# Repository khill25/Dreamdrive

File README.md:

# Dreamdrive
Retro gaming accessories produced by Dreamcraft Industries. Dreamdrive is coming to disc based systems called Dreamdisc! Dreamcast is the first console to get this treatment. Work is in progress to finalize the hardware and software for a first producion run. Stay tuned!

## [Discord](https://discord.gg/sHbhx2qJuK)
Join the discussion and get the latest on Dreamdrive status. Chat with other hackers. Have ideas on a new Dreamdrive product? Come and let me know. 

# Dreamdumper64
New Dreamdumper64 hardware files have been checked in! Navigate to `N64/hw/cart_tester/pc64` for the latest kicad project files.

# Projects
Current project status

| Project | Platform | Purpose  | Status | Notes |
| ------------- | ------------- | ------------- | ------------- | ------------- |
| Dreamdumper64 | N64 | Backup your cartridges | Finished | Completed units are available [here](https://dreamcraftindustries.com/products/dreamdumper64-assembled)!|
| Dreamdisc | Dreamcast | Dreamdive ODE For Dreamcast | Prototype/v3 | Repo files wont boot yet but the design has been verified and will be available soon |
| Dreamdrive Advance | GBA | Developer rom cart | Prototype/v2 | Waiting for new board designs with support for faster psram. Current PSRAM on the qspi bus isn't fast enough to service the cart |
| Super Dreamdrive | SNES | Developer rom cart | Prototype/v1 | Drafted prototype hardware and software. No idea if this is working |

### License
This project is licensed under the [Dreamdrive Open Hardware License v1.0](./LICENSE).  
You are free to learn from, modify, and remix this design for non-commercial purposes with attribution.  
Commercial use requires permission — reach out to kaili [at] dreamcraftindustries [dot] com.

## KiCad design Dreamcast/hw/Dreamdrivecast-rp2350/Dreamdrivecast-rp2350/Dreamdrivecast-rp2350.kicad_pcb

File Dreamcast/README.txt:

Dreamcast GD-ROM replacement. WIP! Untested and not in production state!!!

Will use RP2040s and SD Card to emulate the gdrom drive.

LICENSE: BSD-2-Clause
Copyright (c) 2023 Kaili Hill

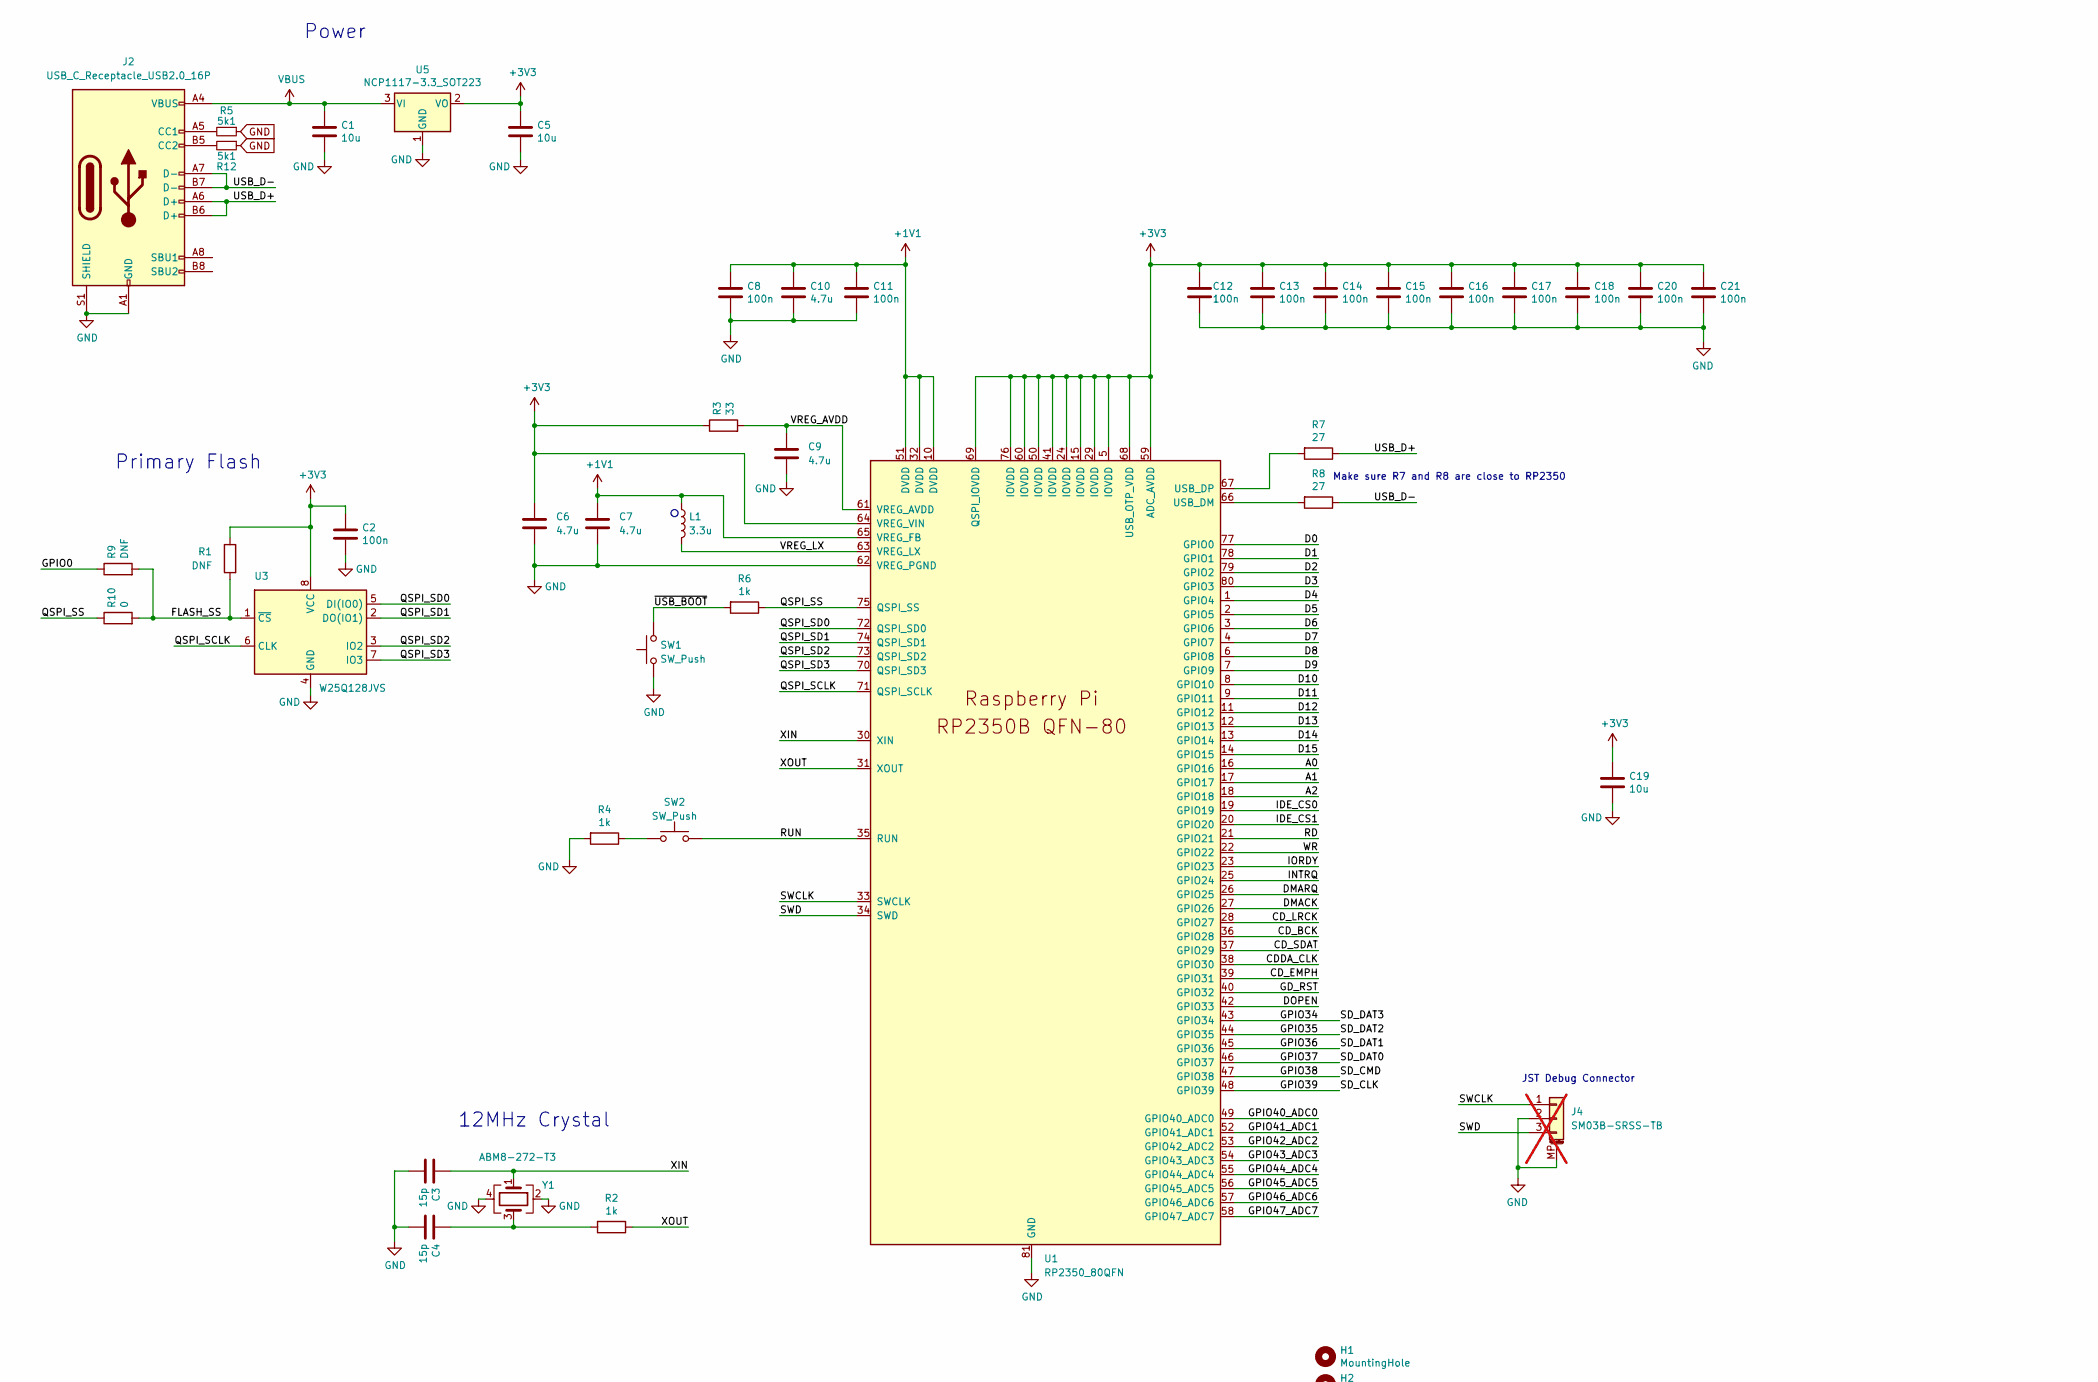
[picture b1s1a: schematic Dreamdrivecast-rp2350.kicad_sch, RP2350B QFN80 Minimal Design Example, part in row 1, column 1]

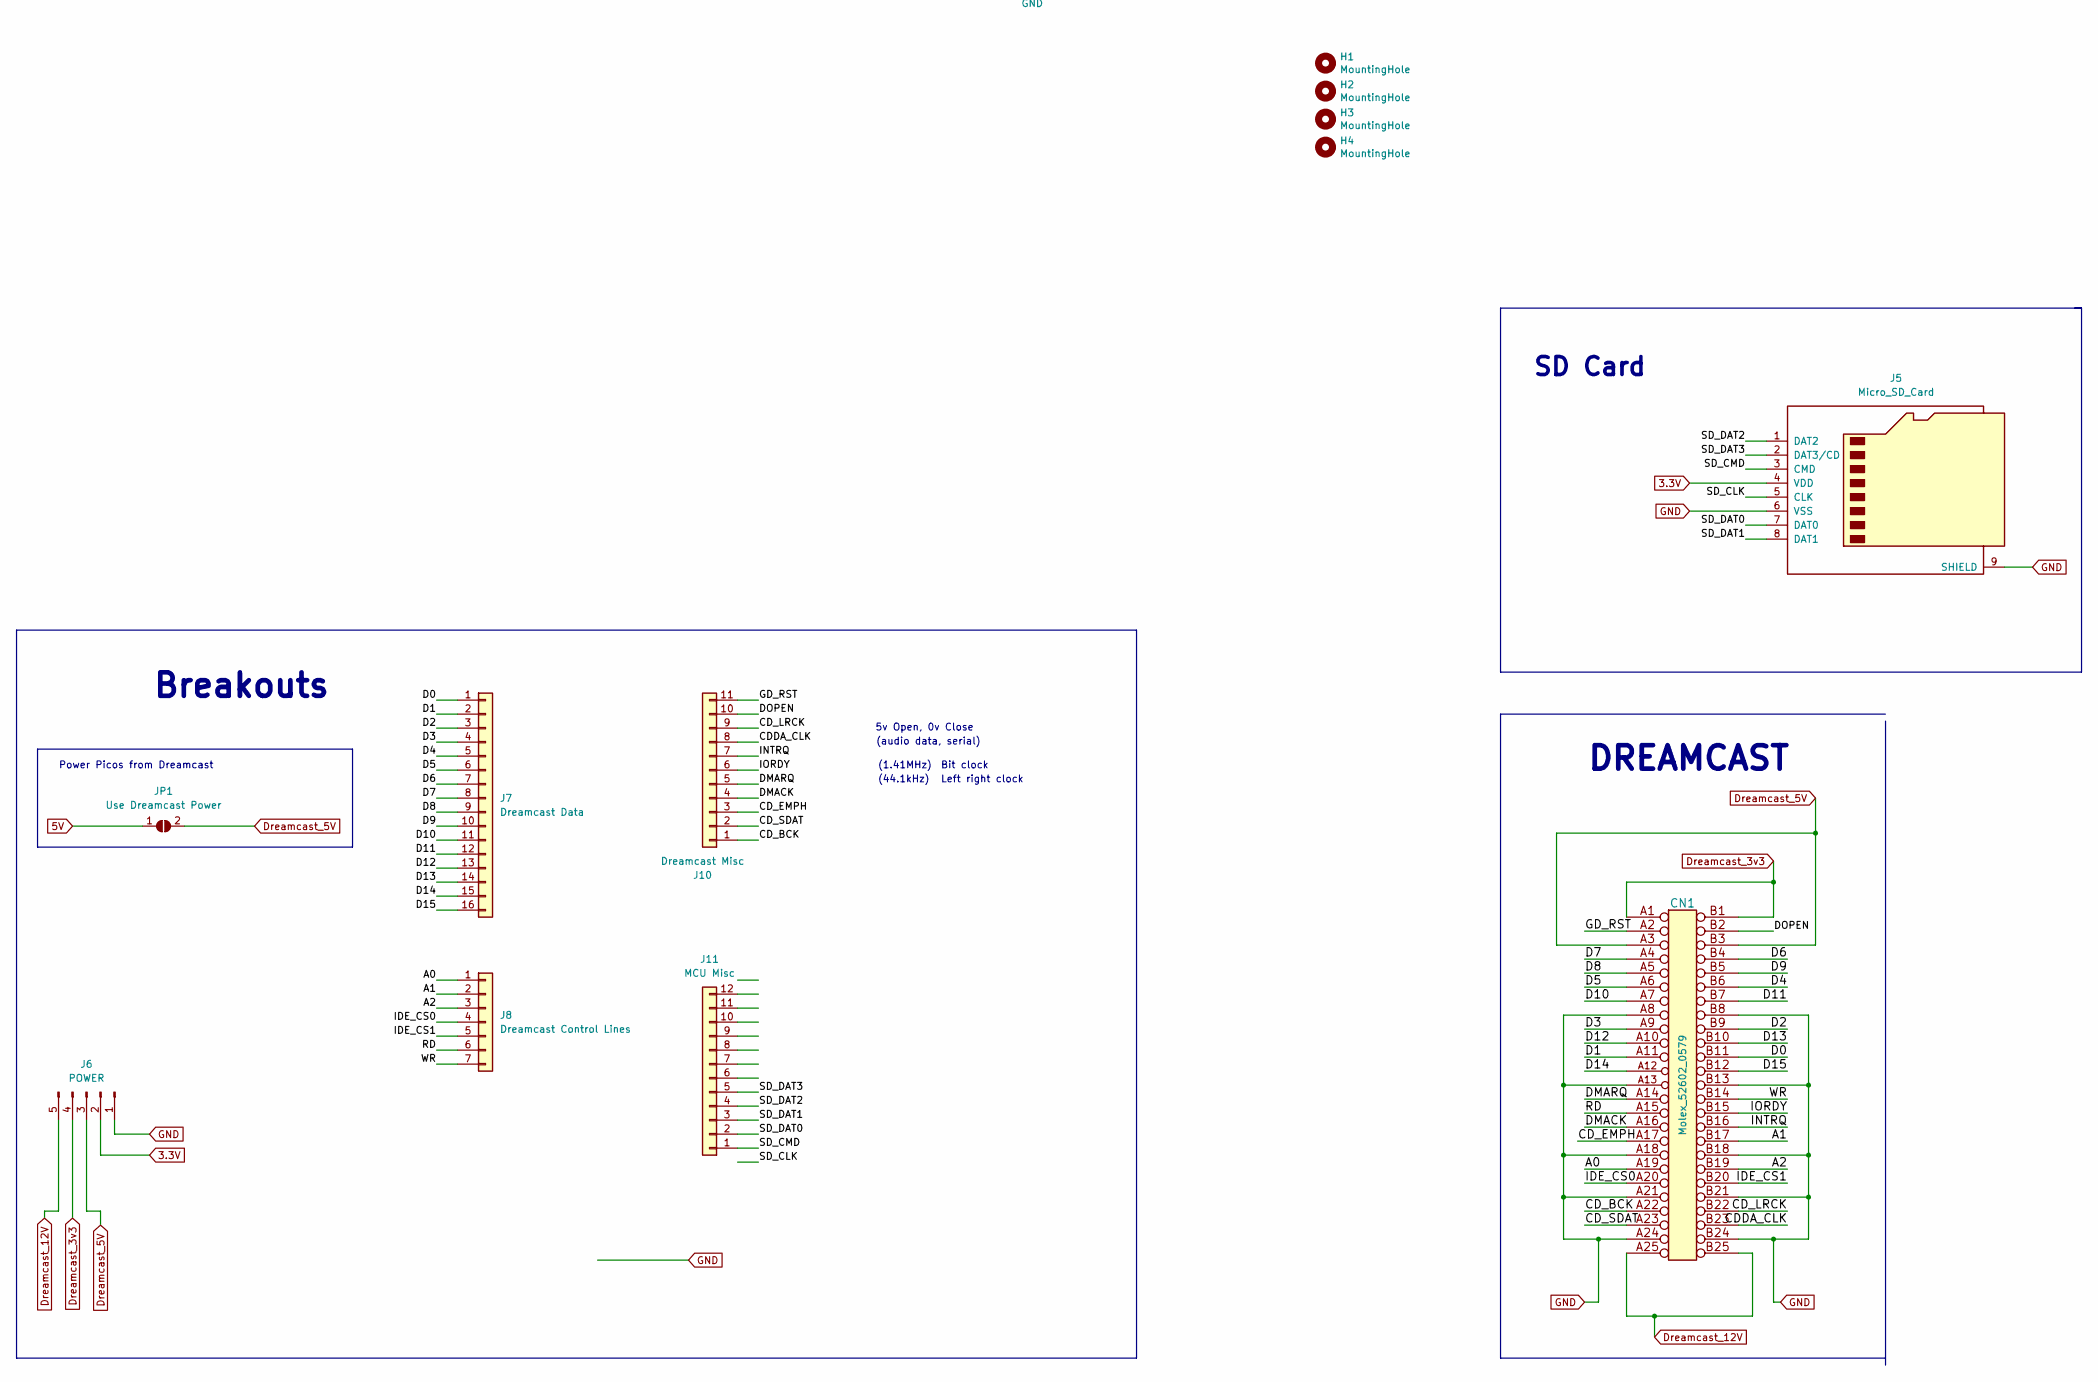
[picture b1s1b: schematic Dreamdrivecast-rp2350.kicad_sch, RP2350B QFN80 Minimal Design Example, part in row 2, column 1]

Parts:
C1, C5, C19: 10u; C_0805_2012Metric
C2, C8, C11, C12, C13, C14, C15, C16, C17, C18, C20, C21: 100n; C_0402_1005Metric
C3, C4: 15p; C_0402_1005Metric
C6, C7: 4.7u; C_0402_1005Metric_small_pads
C9, C10: 4.7u; C_0402_1005Metric
CN1: Molex_52602_0579; LCSC C588209
H1, H2, H3, H4: MountingHole; MountingHole_2.7mm_M2.5
J2: USB_C_Receptacle_USB2.0_16P; USB_C_Receptacle_HRO_TYPE-C-31-M-12
J4: SM03B-SRSS-TB; JST_SH_SM03B-SRSS-TB_1x03-1MP_P1.00mm_Horizontal; not fitted
J5: Micro_SD_Card; microSD_HC_Molex_104031-0811; MPN 1040310811; LCSC C585350
J6: POWER; PinHeader_1x05_P2.54mm_Vertical
J7: Dreamcast Data; PinHeader_1x16_P2.54mm_Vertical
J8: Dreamcast Control Lines; PinHeader_2x07_P2.54mm_Vertical_SMD
J10: Dreamcast Misc; PinHeader_1x11_P2.54mm_Vertical
J11: MCU Misc; PinHeader_1x12_P2.54mm_Vertical
JP1: Use Dreamcast Power; SolderJumper-2_P1.3mm_Open_RoundedPad1.0x1.5mm
L1: 3.3u; L_pol_2016
R1, R9: DNF; R_0402_1005Metric
R2, R4, R6: 1k; R_0402_1005Metric
R3: 33; R_0402_1005Metric
R5, R12: 5k1; R_0402_1005Metric; LCSC C25905
R7, R8: 27; R_0402_1005Metric
R10: 0; R_0402_1005Metric
SW1, SW2: SW_Push; SW_Push_1P1T_NO_Vertical_Wuerth_434133025816
U1: RP2350_80QFN; RP2350-QFN-80-1EP_10x10_P0.4mm_EP3.4x3.4mm_ThermalVias
U3: W25Q128JVS; SOIC-8_5.23x5.23mm_P1.27mm
U5: NCP1117-3.3_SOT223; SOT-223-3_TabPin2
Y1: ABM8-272-T3; Crystal_SMD_3225-4Pin_3.2x2.5mm

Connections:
3.3V: J5.4 (VDD), J6.2
5V: JP1.1 (A)
+1V1: C7.1, C8.1, C10.1, C11.1, L1.1, U1.10 (DVDD), U1.32 (DVDD), U1.51 (DVDD), U1.65 (VREG_FB)
+3V3: C2.1, C5.1, C6.1, C12.1, C13.1, C14.1, C15.1, C16.1, C17.1, C18.1, C19.1, C20.1, C21.1, R1.1, R3.1, U1.5 (IOVDD), U1.15 (IOVDD), U1.24 (IOVDD), U1.29 (IOVDD), U1.41 (IOVDD), U1.50 (IOVDD), U1.59 (ADC_AVDD), U1.60 (IOVDD), U1.64 (VREG_VIN), U1.68 (USB_OTP_VDD), U1.69 (QSPI_IOVDD), U1.76 (IOVDD), U3.8 (VCC), U5.2 (VO)
/A0: CN1.A19, J8.1, U1.16 (GPIO16)
/A1: CN1.B17, J8.2, U1.17 (GPIO17)
/A2: CN1.B19, J8.3, U1.18 (GPIO18)
/CDDA_CLK: CN1.B23, J10.8, U1.38 (GPIO30)
/CD_BCK: CN1.A22, J10.1, U1.36 (GPIO28)
/CD_EMPH: CN1.A17, J10.3, U1.39 (GPIO31)
/CD_LRCK: CN1.B22, J10.9, U1.28 (GPIO27)
/CD_SDAT: CN1.A23, J10.2, U1.37 (GPIO29)
/D0: CN1.B11, J7.1, U1.77 (GPIO0)
/D1: CN1.A11, J7.2, U1.78 (GPIO1)
/D2: CN1.B9, J7.3, U1.79 (GPIO2)
/D3: CN1.A9, J7.4, U1.80 (GPIO3)
/D4: CN1.B6, J7.5, U1.1 (GPIO4)
/D5: CN1.A6, J7.6, U1.2 (GPIO5)
/D6: CN1.B4, J7.7, U1.3 (GPIO6)
/D7: CN1.A4, J7.8, U1.4 (GPIO7)
/D8: CN1.A5, J7.9, U1.6 (GPIO8)
/D9: CN1.B5, J7.10, U1.7 (GPIO9)
/D10: CN1.A7, J7.11, U1.8 (GPIO10)
/D11: CN1.B7, J7.12, U1.9 (GPIO11)
/D12: CN1.A10, J7.13, U1.11 (GPIO12)
/D13: CN1.B10, J7.14, U1.12 (GPIO13)
/D14: CN1.A12, J7.15, U1.13 (GPIO14)
/D15: CN1.B12, J7.16, U1.14 (GPIO15)
/DMACK: CN1.A16, J10.4, U1.27 (GPIO26)
/DMARQ: CN1.A14, J10.5, U1.26 (GPIO25)
/DOPEN: CN1.B2, J10.10, U1.42 (GPIO33)
/FLASH_SS: R1.2, R9.2, R10.2, U3.1 (~CS)
/GD_RST: CN1.A2, J10.11, U1.40 (GPIO32)
/GPIO0: R9.1
/GPIO34: J5.2 (DAT3/CD), J11.5, U1.43 (GPIO34)
/GPIO35: J5.1 (DAT2), J11.4, U1.44 (GPIO35)
/GPIO36: J5.8 (DAT1), J11.3, U1.45 (GPIO36)
/GPIO37: J5.7 (DAT0), J11.2, U1.46 (GPIO37)
/GPIO38: J5.3 (CMD), J11.1, U1.47 (GPIO38)
/GPIO39: J5.5 (CLK), U1.48 (GPIO39)
/GPIO40_ADC0: U1.49 (GPIO40_ADC0)
/GPIO41_ADC1: U1.52 (GPIO41_ADC1)
/GPIO42_ADC2: U1.53 (GPIO42_ADC2)
/GPIO43_ADC3: U1.54 (GPIO43_ADC3)
/GPIO44_ADC4: U1.55 (GPIO44_ADC4)
/GPIO45_ADC5: U1.56 (GPIO45_ADC5)
/GPIO46_ADC6: U1.57 (GPIO46_ADC6)
/GPIO47_ADC7: U1.58 (GPIO47_ADC7)
/IDE_CS0: CN1.A20, J8.4, U1.19 (GPIO19)
/IDE_CS1: CN1.B20, J8.5, U1.20 (GPIO20)
/INTRQ: CN1.B16, J10.7, U1.25 (GPIO24)
/IORDY: CN1.B15, J10.6, U1.23 (GPIO23)
/QSPI_SCLK: U1.71 (QSPI_SCLK), U3.6 (CLK)
/QSPI_SD0: U1.72 (QSPI_SD0), U3.5 (DI(IO0))
/QSPI_SD1: U1.74 (QSPI_SD1), U3.2 (DO(IO1))
/QSPI_SD2: U1.73 (QSPI_SD2), U3.3 (IO2)
/QSPI_SD3: U1.70 (QSPI_SD3), U3.7 (IO3)
/QSPI_SS: R6.1, R10.1, U1.75 (QSPI_SS)
/RD: CN1.A15, J8.6, U1.21 (GPIO21)
/RUN: SW2.2, U1.35 (RUN)
/SWCLK: J4.1, U1.33 (SWCLK); also elsewhere on the board
/SWD: J4.3, U1.34 (SWD); also elsewhere on the board
/USB_D+: J2.A6 (D+), J2.B6 (D+), R7.1
/USB_D-: J2.A7 (D-), J2.B7 (D-), R8.1
/VREG_AVDD: C9.1, R3.2, U1.61 (VREG_AVDD)
/VREG_LX: L1.2, U1.63 (VREG_LX)
/WR: CN1.B14, J8.7, U1.22 (GPIO22)
/XIN: C3.1, U1.30 (XIN), Y1.1
/XOUT: R2.1, U1.31 (XOUT)
/~USB_BOOT: R6.2, SW1.2
Dreamcast_3v3: CN1.A1, CN1.B1, J6.4
Dreamcast_5V: CN1.A3, CN1.B3, J6.3, JP1.2 (B)
Dreamcast_12V: CN1.A25, CN1.B25, J6.5
GND: C1.2, C2.2, C3.2, C4.2, C5.2, C6.2, C7.2, C8.2, C9.2, C10.2, C11.2, C12.2, C13.2, C14.2, C15.2, C16.2, C17.2, C18.2, C19.2, C20.2, C21.2, CN1.A8, CN1.A13, CN1.A18, CN1.A21, CN1.A24, CN1.B8, CN1.B13, CN1.B18, CN1.B21, CN1.B24, J2.A1 (GND), J2.A12 (GND), J2.B1 (GND), J2.B12 (GND), J2.S1 (SHIELD), J4.2, J4.MP (MountPin), J5.6 (VSS), J5.9 (SHIELD), J6.1, R4.2, R5.1, R12.1, SW1.1, U1.62 (VREG_PGND), U1.81 (GND), U3.4 (GND), U5.1 (GND), Y1.2, Y1.4
unnamed: C4.1, R2.2, Y1.3
unnamed: J2.A5 (CC1), R5.2
unnamed: J2.B5 (CC2), R12.2
unnamed: R4.1, SW2.1
unnamed: R8.2, U1.66 (USB_DM)
unnamed: R7.2, U1.67 (USB_DP)
VBUS: C1.1, J2.A4 (VBUS), J2.A9 (VBUS), J2.B4 (VBUS), J2.B9 (VBUS), U5.3 (VI)

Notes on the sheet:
(audio data, serial)
Power Picos from Dreamcast
Power
SD Card
12MHz Crystal
(44.1kHz)
Breakouts
Primary Flash
Bit clock
JST Debug Connector
(1.41MHz)
DREAMCAST
Left right clock
Make sure R7 and R8 are close to RP2350
5v Open, 0v Close

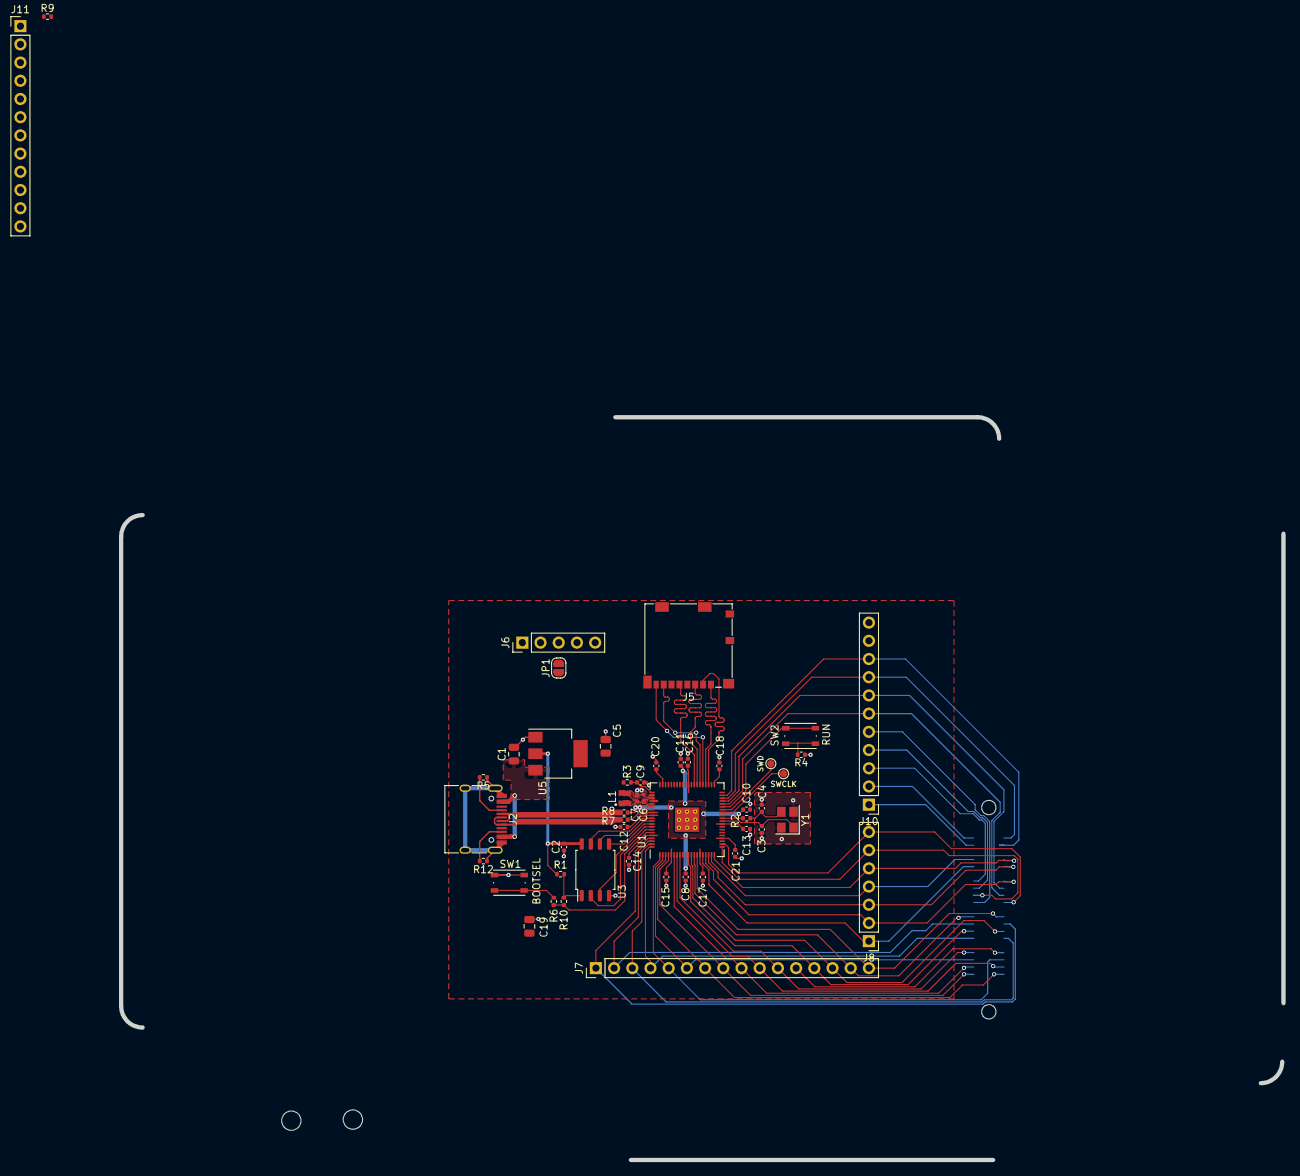
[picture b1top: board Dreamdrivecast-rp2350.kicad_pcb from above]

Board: 2 copper layers, 162.2 x 103.6 mm, 54 parts (1 on the bottom side), 71 nets.

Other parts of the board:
SWCLK: SWD; TestPoint_Pad_D1.0mm
SWD: SWD; TestPoint_Pad_D1.0mm

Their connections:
/SWCLK: SWCLK.1; also elsewhere on the board
/SWD: SWD.1; also elsewhere on the board

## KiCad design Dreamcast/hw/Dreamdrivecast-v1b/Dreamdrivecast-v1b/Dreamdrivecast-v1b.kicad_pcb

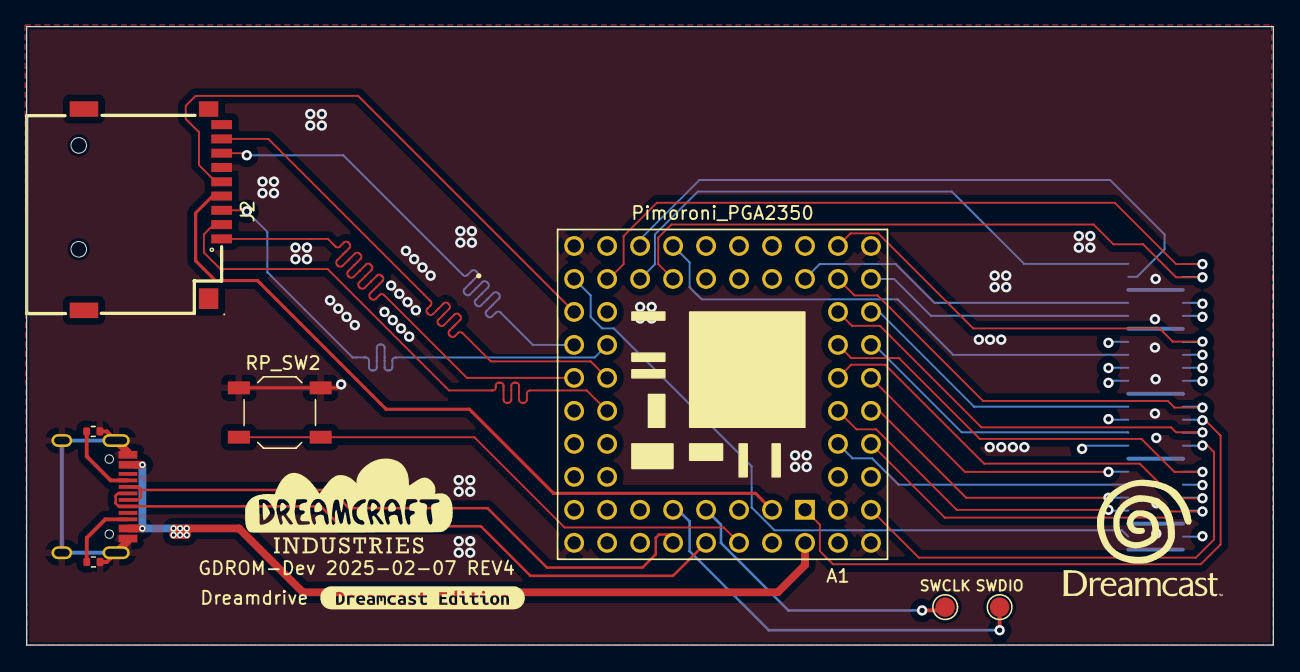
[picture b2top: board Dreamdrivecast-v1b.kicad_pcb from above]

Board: 4 copper layers, 96.0 x 47.6 mm, 11 parts (1 on the bottom side), 53 nets.

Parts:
A1: Pimoroni_PGA2350; pimoroni_pga2350
CN1: Molex_52602_0579
DREAMCRAFT_LOGO: LOGO
J1: USB_C_Receptacle_USB2.0; HRO-TYPE-C-31-M-12_LCSC
J2: Micro_SD_Card; TF-SMD_TF-PUSH
R4, R5: 5k1; R_0402_1005Metric
RP_SW2: SW_Push; SW_SPST_TL3342
SWCLK: TestPoint_Pad_D1.5mm
SWDIO: TestPoint_Pad_D1.5mm
kibuzzard-63F149CE: DDR_DREAMCAST; kibuzzard-63F149CE

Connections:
3V3: A1.55 (3V3), J2.4 (VDD)
/A0: A1.16 (GPIO16), CN1.A19
/A1: A1.17 (GPIO17), CN1.B17
/A2: A1.18 (GPIO18), CN1.B19
/CDDA_CLK: A1.31 (GPIO31), CN1.B23
/CD_BCK: A1.28 (GPIO28), CN1.A22
/CD_EMPH: A1.30 (GPIO30), CN1.A17
/CD_LRCK: A1.27 (GPIO27), CN1.B22
/CD_SDAT: A1.29 (GPIO29), CN1.A23
/D0: A1.0 (GPIO0), CN1.B11
/D1: A1.1 (GPIO1), CN1.A11
/D2: A1.2 (GPIO2), CN1.B9
/D3: A1.3 (GPIO3), CN1.A9
/D4: A1.4 (GPIO4), CN1.B6
/D5: A1.5 (GPIO5), CN1.A6
/D6: A1.6 (GPIO6), CN1.B4
/D7: A1.7 (GPIO7), CN1.A4
/D8: A1.8 (GPIO8), CN1.A5
/D9: A1.9 (GPIO9), CN1.B5
/D10: A1.10 (GPIO10), CN1.A7
/D11: A1.11 (GPIO11), CN1.B7
/D12: A1.12 (GPIO12), CN1.A10
/D13: A1.13 (GPIO13), CN1.B10
/D14: A1.14 (GPIO14), CN1.A12
/D15: A1.15 (GPIO15), CN1.B12
/DMACK: A1.26 (GPIO26), CN1.A16
/DMARQ: A1.25 (GPIO25), CN1.A14
/DOPEN: A1.33 (GPIO33), CN1.B2
/GD_RST: A1.32 (GPIO32), CN1.A2
/IDE_CS0: A1.19 (GPIO19), CN1.A20
/IDE_CS1: A1.20 (GPIO20), CN1.B20
/INTRQ: A1.24 (GPIO24), CN1.B16
/IORDY: A1.23 (GPIO23), CN1.B15
/RD: A1.21 (GPIO21), CN1.A15
/SD_CLK: A1.34 (GPIO34), J2.5 (CLK)
/SD_CMD: A1.35 (GPIO35), J2.3 (CMD)
/SD_DAT0: A1.36 (GPIO36), J2.7 (DAT0)
/SD_DAT1: A1.37 (GPIO37), J2.8 (DAT1)
/SD_DAT2: A1.38 (GPIO38), J2.1 (DAT2)
/SD_DAT3: A1.39 (GPIO39), J2.2 (DAT3/CD)
/SWCLK: A1.51 (SWCLK), SWCLK.1
/SWDIO: A1.49 (SWDIO), SWDIO.1
/WR: A1.22 (GPIO22), CN1.B14
Dreamcast_3v3: CN1.A1, CN1.B1
Dreamcast_5V: CN1.A3, CN1.B3
Dreamcast_12V: CN1.A25, CN1.B25
GND: A1.58 (GND), A1.59 (GND), A1.60 (GND), A1.61 (GND), A1.62 (GND), A1.63 (GND), CN1.A8, CN1.A13, CN1.A18, CN1.A21, CN1.A24, CN1.B8, CN1.B13, CN1.B18, CN1.B21, CN1.B24, J1.A1 (GND), J1.A12 (GND), J1.B1 (GND), J1.B12 (GND), J1.S1 (SHIELD), J2.6 (VSS), R4.1, R5.1, RP_SW2.2
unnamed: J1.A5 (CC1), R5.2
unnamed: J1.B5 (CC2), R4.2
RP1_RUN_PULL: A1.54 (RUN), RP_SW2.1
RP1_USB_D+: A1.52 (USB_DP), J1.A6 (D+), J1.B6 (D+)
RP1_USB_D-: A1.50 (USB_DM), J1.A7 (D-), J1.B7 (D-)
VBUS: A1.57 (VBUS), J1.A4 (VBUS), J1.A9 (VBUS), J1.B4 (VBUS), J1.B9 (VBUS)

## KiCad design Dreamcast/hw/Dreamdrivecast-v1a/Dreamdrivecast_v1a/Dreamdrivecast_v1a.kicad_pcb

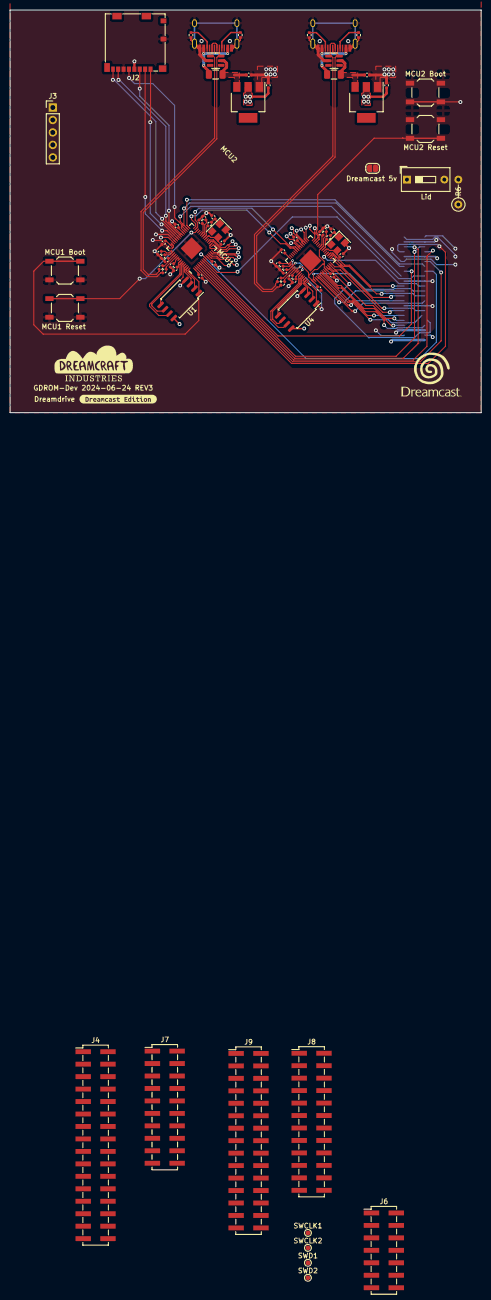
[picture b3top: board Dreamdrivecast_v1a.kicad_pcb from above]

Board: 4 copper layers, 96.0 x 82.0 mm, 74 parts (1 on the bottom side), 98 nets.

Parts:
C1, C2, C5, C6, C7, C8, C9, C10, C11, C16, C17, C20, C21, C22, C23, C24, C25, C26: 100nF; C_0402_1005Metric
C3, C4, C15, C18, C19, C29, C30: 1uF; C_0402_1005Metric
C12, C13, C27, C28: 30pF; C_0402_1005Metric
DREAMCRAFT_LOGO: LOGO
Dreamcast: Molex_52602_0579
F1, F2: 1.1A; Fuse_1206_3216Metric
J1, J5: USB_C_Receptacle_USB2.0; HRO-TYPE-C-31-M-12_LCSC
J2: Micro_SD_Card; microSD_HC_Molex_104031-0811
J3: POWER; PinHeader_1x05_P2.54mm_Vertical
J4: Dreamcast Data; PinHeader_2x16_P2.54mm_Vertical_SMD
J6: Dreamcast Control Lines; PinHeader_2x07_P2.54mm_Vertical_SMD
J7: MCU Databus; PinHeader_2x10_P2.54mm_Vertical_SMD
J8: Dreamcast Misc; PinHeader_2x12_P2.54mm_Vertical_SMD
J9: MCU Misc; PinHeader_2x15_P2.54mm_Vertical_SMD
JP1: Dreamcast 5v; SolderJumper-2_P1.3mm_Open_RoundedPad1.0x1.5mm
Lid: Lid; SW_DIP_SPSTx01_Slide_9.78x4.72mm_W7.62mm_P2.54mm
MCU1, MCU2: RP2040; QFN-56-1EP_7x7mm_P0.4mm_EP3.2x3.2mm
MCU1 Boot, MCU1 Reset, MCU2 Boot, MCU2 Reset: SW_Push; SW_SPST_TL3342
R1, R2, R7, R8: 27; R_0402_1005Metric
R3, R9: 1K; R_0402_1005Metric
R4, R5, R10, R11: 5k1; R_0402_1005Metric
R6: R; R_Axial_DIN0207_L6.3mm_D2.5mm_P5.08mm_Vertical
SWCLK1, SWCLK2: Conn_01x01_Female; TestPoint_Pad_D1.0mm
SWD1, SWD2: Conn_01x01_Female; TestPoint_Pad_D1.0mm
U1, U4: W25Q128JVS; SOIC-8_5.23x5.23mm_P1.27mm
U2, U5: AMS1117-3.3; SOT-223
U3, U6: SRV05-4; SOT-23-6
Y1, Y2: Crystal_GND24; Crystal_SMD_3225-4Pin_3.2x2.5mm
kibuzzard-63F149CE: DDR_DREAMCAST; kibuzzard-63F149CE

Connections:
3.3V: C4.2, C5.2, C6.2, C7.2, C8.2, C9.2, C10.2, C11.2, C15.1, C19.2, C20.2, C21.2, C22.2, C23.2, C24.2, C25.2, C26.2, C30.1, J2.4 (VDD), J3.2, MCU1.1 (IOVDD), MCU1.10 (IOVDD), MCU1.22 (IOVDD), MCU1.33 (IOVDD), MCU1.42 (IOVDD), MCU1.43 (ADC_AVDD), MCU1.44 (VREG_IN), MCU1.48 (USB_VDD), MCU1.49 (IOVDD), MCU2.1 (IOVDD), MCU2.10 (IOVDD), MCU2.22 (IOVDD), MCU2.33 (IOVDD), MCU2.42 (IOVDD), MCU2.43 (ADC_AVDD), MCU2.44 (VREG_IN), MCU2.48 (USB_VDD), MCU2.49 (IOVDD), U1.8 (VCC), U2.2 (VO), U4.8 (VCC), U5.2 (VO)
5V: C29.1, F1.1, F2.1, JP1.1 (A), U2.3 (VI), U3.5 (VP), U5.3 (VI), U6.5 (VP)
/A0: Dreamcast.A19, J6.1, MCU1.2 (GPIO0)
/A1: Dreamcast.B17, J6.2, MCU1.3 (GPIO1)
/A2: Dreamcast.B19, J6.3, MCU1.4 (GPIO2)
/CD_BCK: Dreamcast.A22, J8.6
/CD_EMPH: Dreamcast.A17, J8.11
/CD_LRCK: Dreamcast.B22, J8.5
/CD_SDAT: Dreamcast.A23, J8.7
/CS0: Dreamcast.A20, MCU1.5 (GPIO3)
/CS1: Dreamcast.B20, MCU1.6 (GPIO4)
/D0: Dreamcast.B11, J4.1, MCU2.2 (GPIO0)
/D1: Dreamcast.A11, J4.2, MCU2.3 (GPIO1)
/D2: Dreamcast.B9, J4.3, MCU2.4 (GPIO2)
/D3: Dreamcast.A9, J4.4, MCU2.5 (GPIO3)
/D4: Dreamcast.B6, J4.5, MCU2.6 (GPIO4)
/D5: Dreamcast.A6, J4.6, MCU2.7 (GPIO5)
/D6: Dreamcast.B4, J4.7, MCU2.8 (GPIO6)
/D7: Dreamcast.A4, J4.8, MCU2.9 (GPIO7)
/D8: Dreamcast.A5, J4.9, MCU2.11 (GPIO8)
/D9: Dreamcast.B5, J4.10, MCU2.12 (GPIO9)
/D10: Dreamcast.A7, J4.11, MCU2.13 (GPIO10)
/D11: Dreamcast.B7, J4.12, MCU2.14 (GPIO11)
/D12: Dreamcast.A10, J4.13, MCU2.15 (GPIO12)
/D13: Dreamcast.B10, J4.14, MCU2.16 (GPIO13)
/D14: Dreamcast.A12, J4.15, MCU2.17 (GPIO14)
/D15: Dreamcast.B12, J4.16, MCU2.18 (GPIO15)
/DATABUS_D0: J7.1, MCU1.11 (GPIO8), MCU2.27 (GPIO16)
/DATABUS_D1: J7.2, MCU1.12 (GPIO9), MCU2.28 (GPIO17)
/DATABUS_D2: J7.3, MCU1.13 (GPIO10), MCU2.29 (GPIO18)
/DATABUS_D3: J7.4, MCU1.14 (GPIO11), MCU2.30 (GPIO19)
/DATABUS_D4: J7.5, MCU1.15 (GPIO12), MCU2.31 (GPIO20)
/DATABUS_D5: J7.6, MCU1.16 (GPIO13), MCU2.32 (GPIO21)
/DATABUS_D6: J7.7, MCU1.17 (GPIO14), MCU2.34 (GPIO22)
/DATABUS_D7: J7.8, MCU1.18 (GPIO15), MCU2.35 (GPIO23)
/DATABUS_SIGNAL_READ: J7.9, MCU1.27 (GPIO16), MCU2.36 (GPIO24)
/DATABUS_SIGNAL_WRITE: J7.10, MCU1.28 (GPIO17), MCU2.37 (GPIO25)
/DMACK: Dreamcast.A16, J8.4, MCU1.30 (GPIO19)
/DMARQ: Dreamcast.A14, J8.3, MCU1.31 (GPIO20)
/DOPEN: Dreamcast.B2, J8.8, Lid.2 (B), R6.2
/INTRQ: Dreamcast.B16, J8.2, MCU1.29 (GPIO18)
/IORDY: Dreamcast.B15, J8.1, MCU1.9 (GPIO7)
/MCU1_GPIO27: J9.7, MCU1.39 (GPIO27_ADC1)
/MCU1_GPIO28: J9.8, MCU1.40 (GPIO28_ADC2)
/MCU1_GPIO29: J9.9, MCU1.41 (GPIO29_ADC3)
/MCU2_GPIO26: J9.10, MCU2.38 (GPIO26_ADC0)
/MCU2_GPIO27: J9.11, MCU2.39 (GPIO27_ADC1)
/MCU2_GPIO28: J9.12, MCU2.40 (GPIO28_ADC2)
/MCU2_GPIO29: J9.13, MCU2.41 (GPIO29_ADC3)
/RD: Dreamcast.A15, J6.4, MCU1.7 (GPIO5)
/SD_CLK: J2.5 (CLK), J9.1, MCU1.32 (GPIO21)
/SD_CMD: J2.3 (CMD), J9.2, MCU1.34 (GPIO22)
/SD_DAT0: J2.7 (DAT0), J9.3, MCU1.35 (GPIO23)
/SD_DAT1: J2.8 (DAT1), J9.4, MCU1.36 (GPIO24)
/SD_DAT2: J2.1 (DAT2), J9.5, MCU1.37 (GPIO25)
/SD_DAT3: J2.2 (DAT3/CD), J9.6, MCU1.38 (GPIO26_ADC0)
/WR: Dreamcast.B14, J6.5, MCU1.8 (GPIO6)
Dreamcast_3v3: Dreamcast.A1, Dreamcast.B1, J3.4, JP1.2 (B)
Dreamcast_5V: Dreamcast.A3, Dreamcast.B3, J3.3
Dreamcast_12V: Dreamcast.A25, Dreamcast.B25, J3.5
GND: C1.1, C2.1, C3.1, C4.1, C5.1, C6.1, C7.1, C8.1, C9.1, C10.1, C11.1, C12.2, C13.2, C15.2, C16.1, C17.1, C18.1, C19.1, C20.1, C21.1, C22.1, C23.1, C24.1, C25.1, C26.1, C27.2, C28.2, C29.2, C30.2, Dreamcast.A8, Dreamcast.A13, Dreamcast.A18, Dreamcast.A21, Dreamcast.A24, Dreamcast.B8, Dreamcast.B13, Dreamcast.B18, Dreamcast.B21, Dreamcast.B24, J1.A1 (GND), J1.A12 (GND), J1.B1 (GND), J1.B12 (GND), J1.S1 (SHIELD), J2.6 (VSS), J2.9 (SHIELD), J3.1, J4.17, J4.18, J4.19, J4.20, J4.21, J4.22, J4.23, J4.24, J4.25, J4.26, J4.27, J4.28, J4.29, J4.30, J4.31, J4.32, J5.A1 (GND), J5.A12 (GND), J5.B1 (GND), J5.B12 (GND), J5.S1 (SHIELD), J6.8, J6.9, J6.10, J6.11, J6.12, J6.13, J6.14, J7.11, J7.12, J7.13, J7.14, J7.15, J7.16, J7.17, J7.18, J7.19, J7.20, J8.12, J8.13, J8.14, J8.15, J8.16, J8.17, J8.18, J8.19, J8.20, J8.21, J8.22, J9.15, J9.16, J9.17, J9.18, J9.19, J9.20, J9.21, J9.22, J9.23, J9.24, J9.25, J9.26, J9.27, J9.28, Lid.1 (A), MCU1.19 (TESTEN), MCU1.57 (GND), MCU1 Boot.2, MCU1 Reset.2, MCU2.19 (TESTEN), MCU2.57 (GND), MCU2 Boot.2, MCU2 Reset.2, R4.1, R5.1, R10.1, R11.1, U1.4 (GND), U2.1 (GND), U3.2 (VN), U4.4 (GND), U5.1 (GND), U6.2 (VN), Y1.2, Y1.4, Y2.2, Y2.4
unnamed: C13.1, R3.2, Y1.1
unnamed: C28.1, R9.2, Y2.1
unnamed: F1.2, F2.2, J1.A4 (VBUS), J1.A9 (VBUS), J1.B4 (VBUS), J1.B9 (VBUS), J5.A4 (VBUS), J5.A9 (VBUS), J5.B4 (VBUS), J5.B9 (VBUS)
unnamed: J1.A5 (CC1), J5.A5 (CC1), R5.2, R11.2
unnamed: J1.B5 (CC2), J5.B5 (CC2), R4.2, R10.2
unnamed: MCU1.24 (SWCLK), SWCLK1.1
unnamed: MCU1.25 (SWD), SWD1.1
unnamed: MCU1.46 (USB_DM), R2.1
unnamed: MCU1.47 (USB_DP), R1.1
unnamed: C1.2, C2.2, C3.2, MCU1.23 (DVDD), MCU1.45 (VREG_VOUT), MCU1.50 (DVDD)
unnamed: C12.1, MCU1.20 (XIN), Y1.3
unnamed: MCU1.21 (XOUT), R3.1
unnamed: MCU2.24 (SWCLK), SWCLK2.1
unnamed: MCU2.25 (SWD), SWD2.1
unnamed: MCU2.46 (USB_DM), R8.1
unnamed: MCU2.47 (USB_DP), R7.1
unnamed: C16.2, C17.2, C18.2, MCU2.23 (DVDD), MCU2.45 (VREG_VOUT), MCU2.50 (DVDD)
unnamed: C27.1, MCU2.20 (XIN), Y2.3
unnamed: MCU2.21 (XOUT), R9.1
RP1_CLK: MCU1.52 (QSPI_SCLK), U1.6 (CLK)
RP1_CS: MCU1.56 (QSPI_SS), MCU1 Boot.1, U1.1 (~CS)
RP1_RUN_PULL: MCU1.26 (RUN), MCU1 Reset.1
RP1_SD0: MCU1.53 (QSPI_SD0), U1.5 (DI(IO0))
RP1_SD1: MCU1.55 (QSPI_SD1), U1.2 (DO(IO1))
RP1_SD2: MCU1.54 (QSPI_SD2), U1.3 (IO2)
RP1_SD3: MCU1.51 (QSPI_SD3), U1.7 (IO3)
RP1_USB_D+: J1.A6 (D+), J1.B6 (D+), R1.2, U3.1 (IO1)
RP1_USB_D-: J1.A7 (D-), J1.B7 (D-), R2.2, U3.6 (IO4)
RP2_CLK: MCU2.52 (QSPI_SCLK), U4.6 (CLK)
RP2_CS: MCU2.56 (QSPI_SS), MCU2 Boot.1, U4.1 (~CS)
RP2_RUN_PULL: MCU2.26 (RUN), MCU2 Reset.1
RP2_SD0: MCU2.53 (QSPI_SD0), U4.5 (DI(IO0))
RP2_SD1: MCU2.55 (QSPI_SD1), U4.2 (DO(IO1))
RP2_SD2: MCU2.54 (QSPI_SD2), U4.3 (IO2)
RP2_SD3: MCU2.51 (QSPI_SD3), U4.7 (IO3)
RP2_USB_D+: J5.A6 (D+), J5.B6 (D+), R7.2, U6.1 (IO1)
RP2_USB_D-: J5.A7 (D-), J5.B7 (D-), R8.2, U6.6 (IO4)
